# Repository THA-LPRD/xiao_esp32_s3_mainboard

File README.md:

# XIAO ESP32-S3 Main Board PCB
## Main Board PCB for the first project at Technical University of Applied Science Augsburg
### Explanation
This repo contains the KiCad 8 files for the Main Board of the project. \
Necessary files are located in the src folder, whilst the 3D-models, symbols and footprints can be found in the models, symbols, and footprints folders.
### Functionality
The Main Board is designed to be a host board for XIAO ESP32-S3 board. \
XIAO ESP32-S3 Documentation can be found under this link: https://wiki.seeedstudio.com/xiao_esp32s3_getting_started/ \
The PCB is designed to be powered by a battery (I used two Li-Ion 5400 mAh batteries connected in parallel and connected to a 1S 2 MOSFETs BMS). \
The main functionality of the board is to power an e-paper display and upload pictures to it using SPI protocol. The e-paper display in question is this one: https://www.waveshare.com/7.3inch-e-paper-hat-f.htm \
The PCB is equipped with an external button, which I used to refresh the display on demand (show a new picture), a switch that switches between 3.3V and 5V as Vcc for the display, as some Waveshare displays need 5V to operate. \
There are no mounting holes as the PCB is mounted in a 3D printed housing.
### TODOs
The main branch contains the old schematic with no subsheets and is a bit unpleasant to follow. I added subsheets to the feature_subsheets branch but updating the PCB from that schematic will cause problems with the net names and connections.

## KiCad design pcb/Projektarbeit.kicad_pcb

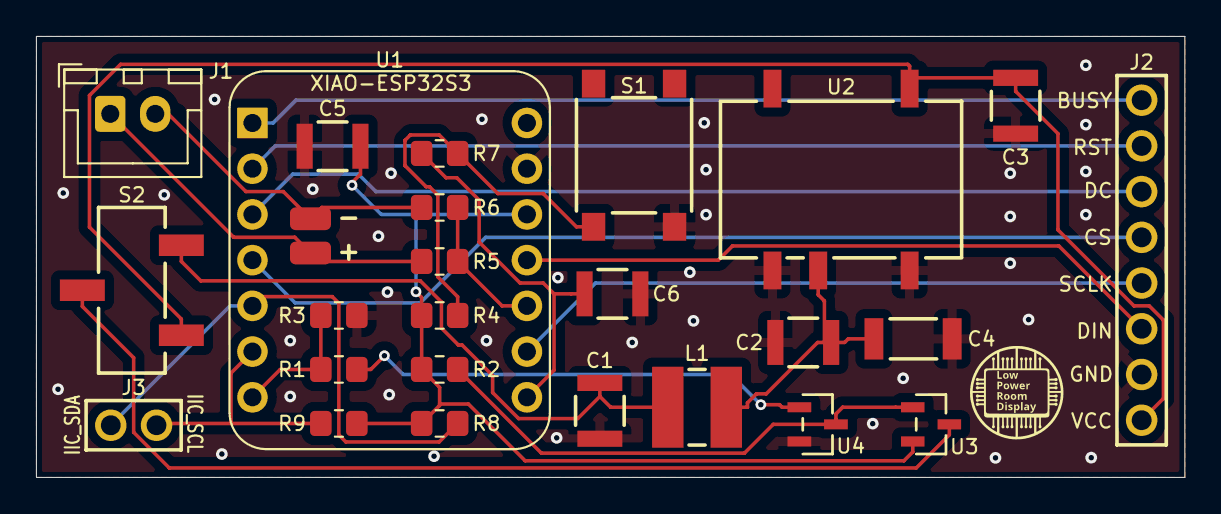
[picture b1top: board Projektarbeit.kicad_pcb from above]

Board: 2 copper layers, 63.8 x 24.5 mm, 25 parts (0 on the bottom side), 22 nets.

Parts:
C1, C2: 4.7µF; WCAP-CSGP_1210_H2.0
C3: 10µF; WCAP-CSGP_1210_H2.0
C4: 470pF; WCAP-CSMH_1808_H2.0
C5, C6: 100nF; WCAP-CSGP_1210_H2.0
J1: JST_XH 01x02; JST_XH_B2B-XH-A_1x02_P2.50mm_Vertical
J2: 61300811121
J3: 61300211121
L1: 6.8µH; WE-PD2_4532
R1: 1kΩ; R_0805_2012Metric_Pad1.20x1.40mm_HandSolder
R2: 100Ω; R_0805_2012Metric_Pad1.20x1.40mm_HandSolder
R3, R4, R7, R8, R9: 10kΩ; R_0805_2012Metric_Pad1.20x1.40mm_HandSolder
R5, R6: 220kΩ; R_0805_2012Metric_Pad1.20x1.40mm_HandSolder
S1: 430182050816
S2: 450406020024
U1: XIAO-ESP32S3; XIAO-Generic-Thruhole-14P-2.54-21X17.8MM
U2: WPME-FISM_SMT-8; WPME-FISM_SMT-8_L13.2W11.4H7.25
U3: SI2307CDS-T1-BE3; SOT-23_VIS
U4: 2N7002K-T1-GE3; SOT_02K-T1-GE3_VIS

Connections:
GND: C1.2, C2.2, C3.2, C4.2, C5.1, C6.2, J2.7, R3.2, S1.2, U1.13 (GND), U2.1, U2.4, U4.2 (S)
unnamed: C1.1, L1.1, S2.3
unnamed: C2.1, C4.1, L1.2, U2.2
unnamed: C3.1, J2.8, S2.1, U2.5
unnamed: J1.1, R5.1, U1.15 (B+)
unnamed: J1.2, R6.2, U1.16 (B-)
unnamed: R4.2, R7.2, S1.1
unnamed: J2.1, U1.1 (PA02_A0_D0)
unnamed: J2.2, U1.2 (PA4_A1_D1)
unnamed: R5.2, R6.1, U1.10 (PA5_A9_D9_MISO)
unnamed: J2.6, U1.11 (PA6_A10_D10_MOSI)
unnamed: J2.5, U1.9 (PA7_A8_D8_SCK)
unnamed: J3.2, R8.1, U1.5 (PA8_A4_D4_SDA)
unnamed: J3.1, R9.1, U1.6 (PA9_A5_D5_SCL)
unnamed: J2.3, U1.3 (PA10_A2_D2)
unnamed: J2.4, U1.4 (PA11_A3_D3)
unnamed: R1.1, R3.1, U1.7 (PB08_A6_D6_TX)
unnamed: C6.1, R7.1, U1.8 (PB09_A7_D7_RX)
unnamed: S2.2, U3.3 (D)
unnamed: R2.1, U3.1 (G), U4.3 (D)
unnamed: R1.2, U4.1 (G)
VCC: C5.2, R2.2, R4.1, R8.2, R9.2, U1.12 (3V3), U3.2 (S)

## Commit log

2024-06-13 deleted unnecessary files
2024-06-24 added html BOM
